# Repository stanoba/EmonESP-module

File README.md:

# EmonESP-module
EmonESP WiFi module based on Wemos D1 mini (PRO)

Thanks to this PCB, you can easily attach Wemos D1 mini board to EmonTX v3.

## PCB v01 (05-2021)

## Schematic

## 3D printed case for EmonTX v3 with EmonESP
STL files could be downloaded from https://www.thingiverse.com/thing:5149944

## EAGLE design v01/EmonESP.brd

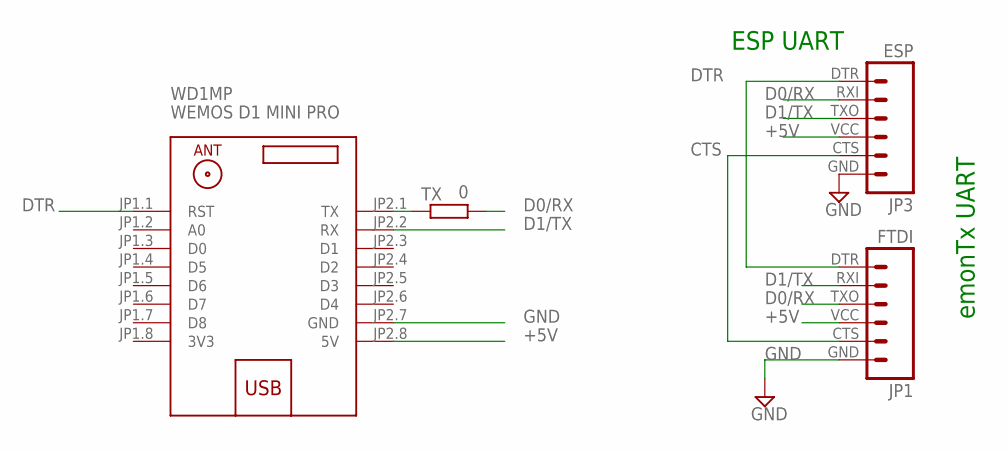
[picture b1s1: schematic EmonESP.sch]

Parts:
JP1: FTDI; FTDI_BASIC
JP3: ESP; FTDI_BASIC
TX: 0; R0603
WD1MP: WEMOS D1 MINI PRO; WEMOS-D1-MINI-PRO

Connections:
3V3: WD1MP.JP1.8 (3V3)
+5V: JP1.VCC (4), JP3.VCC (4), WD1MP.JP2.8 (5V)
CTS: JP1.CTS (5), JP3.CTS (5)
D0/RX: JP1.TXO (3), JP3.RXI (2), TX.2
D1/TX: JP1.RXI (2), JP3.TXO (3), WD1MP.JP2.2 (RX)
DTR: JP1.DTR (1), JP3.DTR (1), WD1MP.JP1.1 (RST)
GND: JP1.GND (6), JP3.GND (6), WD1MP.JP2.7 (GND)
unnamed: TX.1, WD1MP.JP2.1 (TX)

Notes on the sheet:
ESP UART
emonTx UART

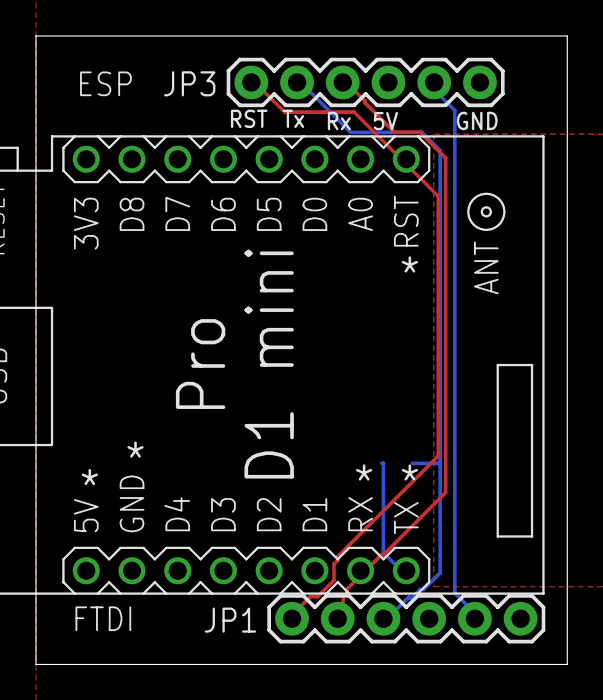
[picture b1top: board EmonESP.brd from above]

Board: 2 copper layers, 29.5 x 34.9 mm, 4 parts (1 on the bottom side), 7 nets.

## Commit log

2021-11-29 folder v01
2021-11-29 v01 release
2021-11-29 Release v01
2021-11-29 Added images and readme file
2021-11-29 Info to STL files

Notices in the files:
parts and their libraries:
diy-modules: Released under the Creative Commons Attribution 4.0 International License: http://creativecommons.org/licenses/by/4.0
